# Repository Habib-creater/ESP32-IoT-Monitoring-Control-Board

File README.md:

# 4-Layer ESP32 IoT Monitoring and Control Board

<p align="center">
  <strong>ESP32-WROOM-32D • Si7021 • Relay • USB • Qwiic • 4-Layer PCB</strong>
</p>

<p align="center">
  A custom 4-layer ESP32-based hardware platform integrating environmental
  sensing, wired connectivity, relay control, USB programming, and
  expansion interfaces.
</p>

<p align="center">
  <a href="docs/IOT_Schematic.pdf">Schematic</a> •
  <a href="bom/IOT_BOM.csv">BOM</a> •
  <a href="manufacturing/gerbers/">Gerbers</a> •
  <a href="hardware/kicad/">KiCad Files</a>
</p>

---

## Overview

The **4-Layer ESP32 IoT Monitoring and Control Board** is a custom
embedded hardware platform built around the **ESP32-WROOM-32D** module.

The board combines environmental sensing through the **Si7021-A20**,
serial and wired interfaces, relay control, USB connectivity, Qwiic
expansion, and general-purpose GPIO in a compact 4-layer PCB design.

The complete hardware package is included in this repository, covering
the native **KiCad project**, electrical schematic, PCB layout, BOM,
Gerber and drill manufacturing files, pick-and-place data, and PCB
documentation.

> **Status:** Design files and manufacturing outputs included.

---

## Quick Access

| Resource | Description |
|---|---|
|  [Schematic PDF](docs/IOT_Schematic.pdf) | Complete electrical schematic |
|  [Bill of Materials](bom/IOT_BOM.csv) | Component BOM |
|  [Gerber & Drill Files](manufacturing/gerbers/) | PCB manufacturing outputs |
|  [KiCad Project](hardware/kicad/) | Native KiCad design files |
|  [PCB Images](docs/images/) | 3D renders and layer views |
|  [Pick-and-Place Data](manufacturing/pick-and-place/) | Component placement data |
|  [ERC / DRC Reports](docs/images/) | Design verification screenshots |

---

## Key Features

| Feature | Details |
|---|---|
| **Main Controller** | ESP32-WROOM-32D |
| **Environmental Sensor** | Si7021-A20 |
| **Sensor Interface** | I²C |
| **Serial / Expansion** | UART / GPIO |
| **Relay Control** | RT314A05 relay |
| **USB** | USB 2.0 Type-C interface |
| **Expansion** | Qwiic connector |
| **PCB** | 4-layer PCB |
| **EDA Software** | KiCad |
| **Manufacturing Data** | Gerber + PTH/NPTH drill files |
| **Assembly Data** | Top and bottom pick-and-place files |

---

## PCB Preview

### 3D Board Render

### Alternative 3D View

### Bottom 3D View

---

## PCB Layer Views

### Front Copper / Layout

### Inner Layer 1

### Inner Layer 2

### Bottom Layer

---

## Hardware Architecture

The design brings together several functional blocks around the ESP32
controller.

### ESP32-WROOM-32D

The **ESP32-WROOM-32D** provides the primary processing and wireless
connectivity platform for the board.

### Environmental Sensing

The **Si7021-A20** provides digital environmental sensing through an
I²C interface.

### Relay Control

A **RT314A05 relay** provides a dedicated switched-output function with
associated transistor drive circuitry.

### USB and Programming

The board includes a **USB Type-C USB 2.0 interface** and associated
USB interface circuitry.

### Qwiic Expansion

A **Qwiic connector** provides an additional I²C expansion interface.

---

## PCB Design

The board is implemented as a **4-layer PCB** using **KiCad**.

### PCB Characteristics

- 4-layer PCB architecture
- ESP32-WROOM-32D module
- Environmental sensor interface
- Relay control circuitry
- USB Type-C interface
- Qwiic expansion
- Dedicated internal copper layers
- Compact component placement
- Through-hole and surface-mount components
- PTH and NPTH manufacturing data

---

## Design Files

The native KiCad project is located in:

[**hardware/kicad/**](hardware/kicad/)

### Main Files

| File | Description |
|---|---|
| `IOT.kicad_pro` | KiCad project |
| `IOT.kicad_sch` | Schematic source |
| `IOT.kicad_pcb` | PCB layout |

---

## Schematic

The exported electrical schematic is available as:

###  [View IOT Schematic PDF](docs/IOT_Schematic.pdf)

The schematic documents the ESP32 controller, environmental sensor,
USB interface, relay control, Qwiic interface,
power circuitry, and associated support components.

---

## Bill of Materials

The current component BOM is available here:

###  [View / Download IOT BOM](bom/IOT_BOM.csv)

The BOM contains the component references, quantities, values,
footprints, and associated component information from the design.

---

## Manufacturing Outputs

The generated manufacturing package is available under:

###  [Gerber & Drill Files](manufacturing/gerbers/)

The package contains:

- Front copper
- Back copper
- Inner copper layer 1
- Inner copper layer 2
- Front solder mask
- Back solder mask
- Front silkscreen
- Back silkscreen
- Front solder paste
- Back solder paste
- Board outline
- PTH drill data
- NPTH drill data
- Gerber job file

---

## Pick-and-Place Data

Assembly placement data is available in:

[**manufacturing/pick-and-place/**](manufacturing/pick-and-place/)

The repository contains separate top-side and bottom-side component
placement files.

---

## Design Verification

Design verification artifacts included with the project:

### ERC

### DRC

---

## Project Status

| Item | Status |
|---|---|
| Schematic | ✅ Completed |
| PCB Layout | ✅ Completed |
| PCB Layer Count | ✅ 4-layer |
| KiCad Project | ✅ Included |
| BOM | ✅ Included |
| Gerber Files | ✅ Generated |
| Drill Files | ✅ Generated |
| Pick-and-Place Data | ✅ Included |
| ERC Documentation | ✅ Included |
| DRC Documentation | ✅ Included |
| PCB Documentation | ✅ Included |

---

## Repository Structure

```text
.
├── hardware/
│   └── kicad/
│       ├── IOT.kicad_pro
│       ├── IOT.kicad_sch
│       └── IOT.kicad_pcb
│
├── manufacturing/
│   ├── gerbers/
│   │   ├── IOT-F_Cu.gbr
│   │   ├── IOT-In1_Cu.gbr
│   │   ├── IOT-In2_Cu.gbr
│   │   ├── IOT-B_Cu.gbr
│   │   ├── IOT-F_Mask.gbr
│   │   ├── IOT-B_Mask.gbr
│   │   ├── IOT-F_Silkscreen.gbr
│   │   ├── IOT-B_Silkscreen.gbr
│   │   ├── IOT-F_Paste.gbr
│   │   ├── IOT-B_Paste.gbr
│   │   ├── IOT-Edge_Cuts.gbr
│   │   ├── IOT-PTH.drl
│   │   ├── IOT-NPTH.drl
│   │   └── IOT-job.gbrjob
│   │
│   └── pick-and-place/
│       ├── IOT-top.pos
│       └── IOT-bottom.pos
│
├── bom/
│   └── IOT_BOM.csv
│
├── docs/
│   ├── images/
│   │   ├── 3D_front_1.png
│   │   ├── 3D_front_2.png
│   │   ├── 3D_BACK.png
│   │   ├── Layout_front_layer.png
│   │   ├── Layout_inner_layer_1.png
│   │   ├── Layout_inner_layer_2.png
│   │   ├── Layout_Bottom_layer.png
│   │   ├── ERC.png
│   │   └── DRC.png
│   │
│   └── IOT_Schematic.pdf
│
├── .gitignore
├── CONTRIBUTING.md
├── LICENSE
└── README.md
```

---

## Acknowledgements

This repository contains the hardware design package for the
4-Layer ESP32 IoT Monitoring and Control Board.

The repository includes the native KiCad source files together with
the associated schematic, PCB documentation, BOM, manufacturing
outputs, and assembly data.

---

## Contributing

Contributions, design reviews, and hardware improvements are welcome.

For proposed revisions, keep the native KiCad design files and
associated documentation aligned with the corresponding hardware
revision.

---

## License

The hardware design files in this repository are licensed under the
**CERN Open Hardware Licence Version 2 - Strongly Reciprocal
(CERN-OHL-S-2.0)**.

The CERN-OHL-S-2.0 licence is a hardware-specific open-source licence
for sharing, modifying, and distributing covered hardware designs.

**Copyright © 2026 Habib Ur Rehman**

See [`LICENSE`](LICENSE) for the licence information associated with
this repository.

---

## Author

### Habib Ur Rehman

**Electronics Engineering**

Embedded systems, PCB design, microcontrollers, electronics hardware,
and hardware development.

### Connect

- **GitHub:** [Habib-creater](https://github.com/Habib-creater)
- **LinkedIn:** [Habib Ur Rehman](https://www.linkedin.com/in/habib-ur-rehman-8321182b4/)

---

<p align="center">
  <strong>4-Layer ESP32 IoT Monitoring and Control Board</strong><br>
  Custom ESP32 Embedded Hardware Platform
</p>

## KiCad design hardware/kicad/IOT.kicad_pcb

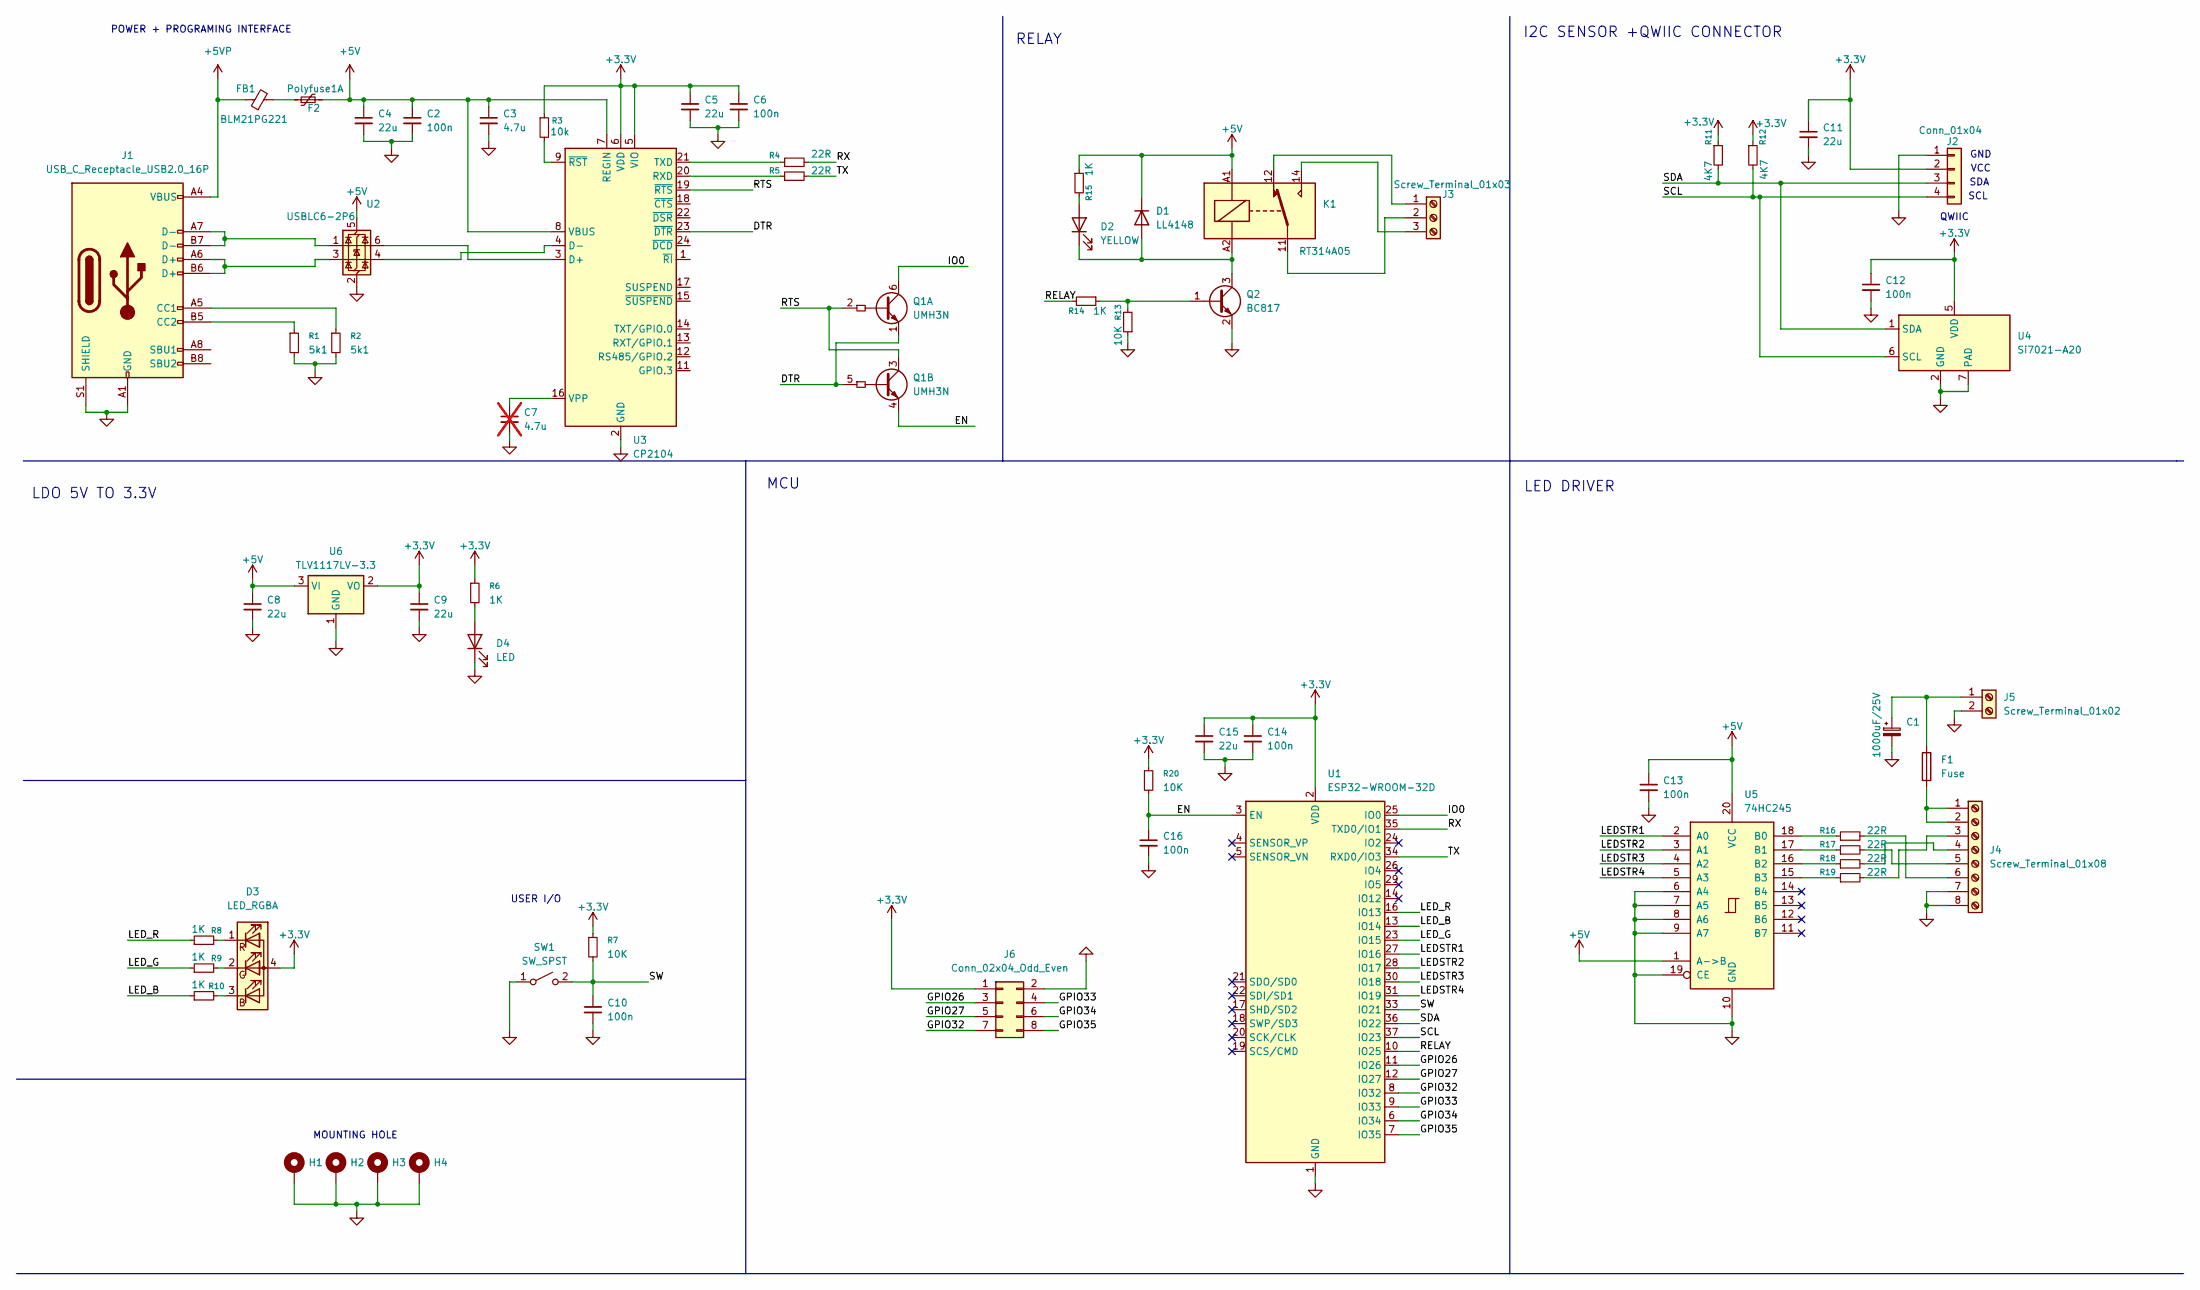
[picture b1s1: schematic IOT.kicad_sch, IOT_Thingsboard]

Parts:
C1: 1000uF/25V; CP_Radial_D10.0mm_P5.00mm
C2, C6, C10, C12, C13, C14, C16: 100n; C_0402_1005Metric_Pad0.74x0.62mm_HandSolder
C3: 4.7u; C_0805_2012Metric_Pad1.18x1.45mm_HandSolder
C4, C5, C8, C9, C11, C15: 22u; C_0805_2012Metric_Pad1.18x1.45mm_HandSolder
C7: 4.7u; C_0805_2012Metric_Pad1.18x1.45mm_HandSolder; not fitted
D1: LL4148; D_MiniMELF
D2: YELLOW; LED_0603_1608Metric_Pad1.05x0.95mm_HandSolder
D3: LED_RGBA; LED_RGB_Wuerth-PLCC4_3.2x2.8mm_150141M173100
D4: LED; LED_0603_1608Metric_Pad1.05x0.95mm_HandSolder
F1: Fuse; 696105003002
F2: Polyfuse1A; Fuse_1206_3216Metric_Pad1.42x1.75mm_HandSolder
FB1: BLM21PG221; L_0805_2012Metric
H1, H2, H3, H4: MountingHole_Pad; MountingHole_3.2mm_M3_Pad_Via
J1: USB_C_Receptacle_USB2.0_16P; USB_C_Receptacle_HRO_TYPE-C-31-M-12
J2: Conn_01x04; SPARKFUN_PRT-14417
J3: Screw_Terminal_01x03; TerminalBlock_Phoenix_MKDS-3-3-5.08_1x03_P5.08mm_Horizontal
J4: Screw_Terminal_01x08; TerminalBlock_Phoenix_MKDS-1,5-8_1x08_P5.00mm_Horizontal
J5: Screw_Terminal_01x02; TerminalBlock_Phoenix_MKDS-1,5-2_1x02_P5.00mm_Horizontal
J6: Conn_02x04_Odd_Even; PinHeader_2x04_P2.54mm_Vertical
K1: RT314A05; Relay_SPDT_Schrack-RT1-16A-FormC_RM5mm
Q1: UMH3N; SOT-363_SC-70-6
Q2: BC817; SOT-23
R1, R2: 5k1; R_0402_1005Metric_Pad0.72x0.64mm_HandSolder
R3: 10k; R_0402_1005Metric_Pad0.72x0.64mm_HandSolder
R4, R5, R16, R17, R18, R19: 22R; R_0402_1005Metric_Pad0.72x0.64mm_HandSolder
R6, R8, R9, R10, R14, R15: 1K; R_0402_1005Metric_Pad0.72x0.64mm_HandSolder
R7, R13, R20: 10K; R_0402_1005Metric_Pad0.72x0.64mm_HandSolder
R11, R12: 4K7; R_0402_1005Metric_Pad0.72x0.64mm_HandSolder
SW1: SW_SPST; SW_Push_1P1T_NO_CK_KMR2
U1: ESP32-WROOM-32D
U2: USBLC6-2P6; SOT-666
U3: CP2104; QFN-24-1EP_4x4mm_P0.5mm_EP2.6x2.6mm
U4: Si7021-A20; DFN-6-1EP_3x3mm_P1mm_EP1.5x2.4mm
U5: 74HC245; DIP-20_W7.62mm
U6: TLV1117LV-3.3; SOT-223-3_TabPin2

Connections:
+3.3V: C5.1, C6.1, C9.1, C11.1, C12.1, C14.1, C15.1, D3.4 (A), J2.2, J6.1, R3.1, R6.1, R7.1, R11.1, R12.1, R20.1, U1.2 (VDD), U3.5 (VIO), U3.6 (VDD), U4.5 (VDD), U6.2 (VO); also elsewhere on the board
+5V: C2.1, C3.1, C4.1, C8.1, C13.1, D1.1 (K), F2.2, K1.A1, R15.1, U2.5 (VBUS), U3.7 (REGIN), U3.8 (VBUS), U5.1 (A->B), U5.20 (VCC), U6.3 (VI)
+5VP: FB1.1, J1.A4 (VBUS), J1.A9 (VBUS), J1.B4 (VBUS), J1.B9 (VBUS)
/DTR: Q1.1 (E1), Q1.5 (B2), U3.23 (~DTR)
/EN: C16.1, Q1.4 (E2), R20.2, U1.3 (EN)
/GPIO26: J6.3, U1.11 (IO26); also elsewhere on the board
/GPIO27: J6.5, U1.12 (IO27); also elsewhere on the board
/GPIO32: J6.7, U1.8 (IO32); also elsewhere on the board
/GPIO33: J6.4, U1.9 (IO33); also elsewhere on the board
/GPIO34: J6.6, U1.6 (IO34); also elsewhere on the board
/GPIO35: J6.8, U1.7 (IO35); also elsewhere on the board
/IO0: Q1.6 (C1), U1.25 (IO0)
/LEDSTR1: U1.27 (IO16), U5.2 (A0)
/LEDSTR2: U1.28 (IO17), U5.3 (A1)
/LEDSTR3: U1.30 (IO18), U5.4 (A2)
/LEDSTR4: U1.31 (IO19), U5.5 (A3)
/LED_B: R10.1, U1.13 (IO14)
/LED_G: R9.1, U1.23 (IO15)
/LED_R: R8.1, U1.16 (IO13)
/RELAY: R14.2, U1.10 (IO25)
/RTS: Q1.2 (B1), Q1.3 (C2), U3.19 (~RTS)
/RX: R4.2, U1.35 (TXD0/IO1)
/SCL: J2.4, R12.2, U1.37 (IO23), U4.6 (SCL)
/SDA: J2.3, R11.2, U1.36 (IO22), U4.1 (SDA)
/SW: C10.1, R7.2, SW1.2 (B), U1.33 (IO21)
/TX: R5.2, U1.34 (RXD0/IO3)
GND: C1.2, C2.2, C3.2, C4.2, C5.2, C6.2, C7.2, C8.2, C9.2, C10.2, C11.2, C12.2, C13.2, C14.2, C15.2, C16.2, D4.1 (K), H1.1, H2.1, H3.1, H4.1, J1.A1 (GND), J1.A12 (GND), J1.B1 (GND), J1.B12 (GND), J1.S1 (SHIELD), J2.1, J4.7, J4.8, J5.2, J6.2, Q2.2 (E), R1.2, R2.2, R13.1, SW1.1 (A), U1.1 (GND), U1.15 (GND), U1.38 (GND), U1.39 (GND), U2.2 (GND), U3.2 (GND), U3.25 (GND), U4.2 (GND), U4.7 (PAD), U5.6 (A4), U5.7 (A5), U5.8 (A6), U5.9 (A7), U5.10 (GND), U5.19 (CE), U6.1 (GND); also elsewhere on the board
unnamed: D1.2 (A), D2.1 (K), K1.A2, Q2.3 (C)
unnamed: D2.2 (A), R15.2
unnamed: D3.3 (BK), R10.2
unnamed: D3.2 (GK), R9.2
unnamed: D3.1 (RK), R8.2
unnamed: D4.2 (A), R6.2
unnamed: F2.1, FB1.2
unnamed: J1.A5 (CC1), R2.1
unnamed: J1.B5 (CC2), R1.1
unnamed: J1.A6 (D+), J1.B6 (D+), U2.3 (I/O2)
unnamed: J1.A7 (D-), J1.B7 (D-), U2.1 (I/O1)
unnamed: J3.1, K1.12
unnamed: J3.2, K1.11
unnamed: J3.3, K1.14
unnamed: F1.2, J4.1, J4.2
unnamed: J4.3, R19.2
unnamed: J4.4, R18.2
unnamed: J4.5, R17.2
unnamed: J4.6, R16.2
unnamed: C1.1, F1.1, J5.1
unnamed: Q2.1 (B), R13.2, R14.1
unnamed: U2.6 (I/O1), U3.3 (D+)
unnamed: U2.4 (I/O2), U3.4 (D-)
unnamed: R5.1, U3.20 (RXD)
unnamed: R4.1, U3.21 (TXD)
unnamed: C7.1, U3.16 (VPP)
unnamed: R3.2, U3.9 (~RST)
unnamed: R16.1, U5.18 (B0)
unnamed: R17.1, U5.17 (B1)
unnamed: R18.1, U5.16 (B2)
unnamed: R19.1, U5.15 (B3)

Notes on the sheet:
LDO 5V TO 3.3V
POWER + PROGRAMING INTERFACE
LED DRIVER
QWIIC
MOUNTING HOLE
MCU
RELAY
SCL
GND
VCC
SDA
USER I/O
I2C SENSOR +QWIIC CONNECTOR

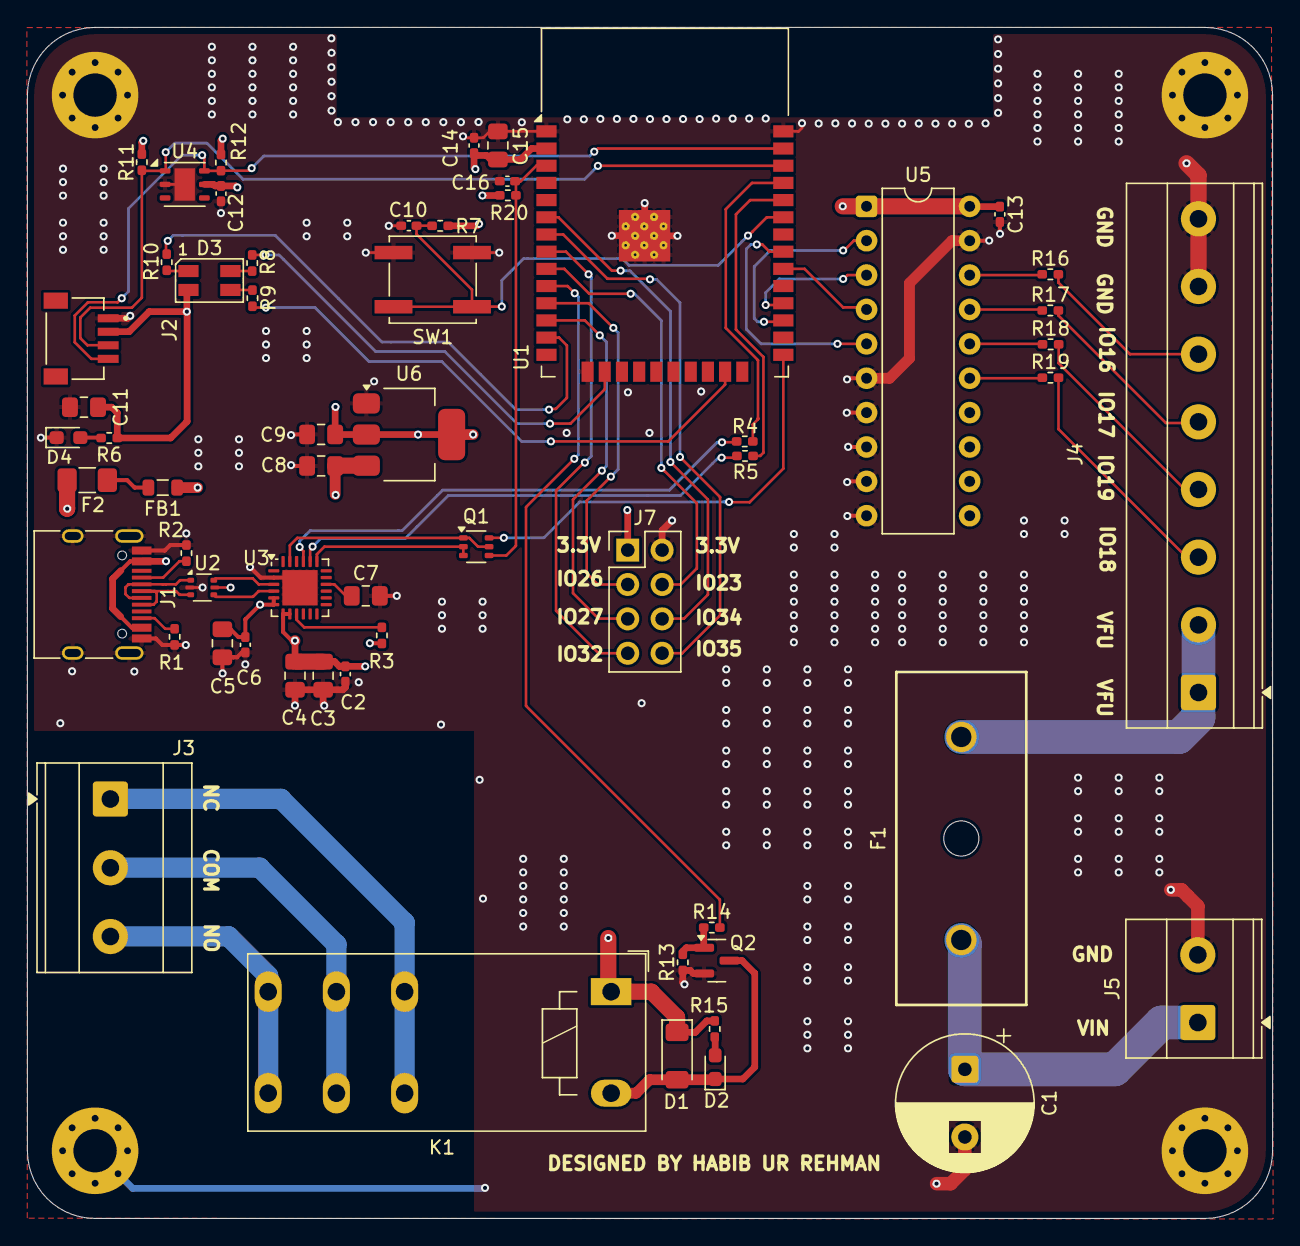
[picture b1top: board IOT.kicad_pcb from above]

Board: 4 copper layers, 92.0 x 88.0 mm, 63 parts (0 on the bottom side), 58 nets.

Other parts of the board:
J7: Conn_02x04_Odd_Even; PinHeader_2x04_P2.54mm_Vertical

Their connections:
+3.3V: J7.1; also elsewhere on the board
/GPIO26: J7.3; also elsewhere on the board
/GPIO27: J7.5; also elsewhere on the board
/GPIO32: J7.7; also elsewhere on the board
/GPIO33: J7.4; also elsewhere on the board
/GPIO34: J7.6; also elsewhere on the board
/GPIO35: J7.8; also elsewhere on the board
GND: J7.2; also elsewhere on the board

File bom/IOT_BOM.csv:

Reference,Qty,Value,DNP,Exclude from BOM,Exclude from Board,Footprint,Description,Manufacturer,Manufacturer Part No ,Supplier,Supplier Part No,Supplier Link,
C1,1,1000uF/25V,,,,Capacitor_THT:CP_Radial_D10.0mm_P5.00mm,CAP ALUM POLY 1000UF 20% 25V TH,KEMET,A750MV108M1EAAE014,DigiKey,399-A750MV108M1EAAE014-ND,https://www.digikey.com/en/products/detail/kemet/A750MV108M1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,
"C2,C6,C10,C12,C13,C14,C16",7,100n,,,,Capacitor_SMD:C_0402_1005Metric_Pad0.74x0.62mm_HandSolder,CAP CER 100NF 10V X7R 0402,Samsung Electro-Mechanics,CL05B104KP5VPNC,DigiKey,1276-CL05B104KP5VPNCCT-ND,https://www.digikey.com/en/products/detail/samsung-electro-m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,
C3,1,4.7u,,,,Capacitor_SMD:C_0805_2012Metric_Pad1.18x1.45mm_HandSolder,CAP CER 4.7UF 16V X5R 0805,Samsung Electro-Mechanics,CL21A475KOFNNNE,DigiKey,1276-1065-1-ND,https://www.digikey.com/en/products/detail/tdk/C1005X5R1A475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,https://www.digikey.com/en/products/detail/samsung-electro-m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
"C4,C5,C8,C9,C11,C15",6,22u,,,,Capacitor_SMD:C_0805_2012Metric_Pad1.18x1.45mm_HandSolder,CAP CER 22UF 16V X5R 0805,Samsung Electro-Mechanics,CL21A226KOQNNNE,DigiKey,1276-6526-1-ND,https://www.digikey.com/en/products/detail/samsung-electro-m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,
C7,1,4.7u,DNP,Excluded from BOM,,Capacitor_SMD:C_0805_2012Metric_Pad1.18x1.45mm_HandSolder,CAP CER 4.7UF 16V X5R 0805,Samsung Electro-Mechanics,CL21A475KOFNNNE,DigiKey,1276-1065-1-ND,https://www.digikey.com/en/products/detail/samsung-electro-m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,
D1,1,LL4148,,,,Diode_SMD:D_MiniMELF,SWITCHING DIODE 0.3A 100V SOD-80,Lumimax Optoelectronic Technology,LL4148,DigiKey,4491-LL4148TR-ND,https://www.digikey.com/en/products/detail/lumimax-optoelect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,
D2,1,YELLOW,,,,LED_SMD:LED_0603_1608Metric_Pad1.05x0.95mm_HandSolder,LED YELLOW 0603 SMD,Vishay Semiconductor Opto Division,TLMY1100-GS15,DigiKey,751-TLMY1100-GS15CT-ND,https://www.digikey.com/en/products/detail/vishay-semiconduc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,
D3,1,LED_RGBA,,,,LED_SMD:LED_RGB_Wuerth-PLCC4_3.2x2.8mm_150141M173100,LED RGB CLEAR 3528 SMD,Würth Elektronik,150141M173100,DigiKey,732-4998-1-ND,https://www.digikey.com/en/products/detail/w%C3%BCrth-elektr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,
D4,1,LED,,,,LED_SMD:LED_0603_1608Metric_Pad1.05x0.95mm_HandSolder,LED RED 0603 SMD,Vishay Semiconductor Opto Division,VLMS1300-GS08,DigiKey,VLMS1300-GS08CT-ND,https://www.digikey.com/en/products/detail/vishay-semiconduc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,
F1,1,Fuse,,,,Fuse_1:696105003002,FUSEHOLDER BLOCKS - PCB - CLIP C,Würth Elektronik,6.96E+11,DigiKey,732-11373-ND,https://www.digikey.com/en/products/detail/w%C3%BCrth-elektr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,
F2,1,Polyfuse1A,,,,Fuse:Fuse_1206_3216Metric_Pad1.42x1.75mm_HandSolder,"Polymeric PTC Resettable Fuse 8V 1.1 A Ih Surface Mount 1206 (3216 Metric), Concave",Littelfuse Inc.,1206L110THYR,DigiKey,F3371CT-ND,https://www.digikey.com/en/products/detail/littelfuse-inc/12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,
FB1,1,BLM21PG221,,,,Inductor_SMD:L_0805_2012Metric,FERRITE BEAD 220 OHM 0805 1LN,Murata Electronics,BLM21PG221SN1D,DigiKey,490-1054-1-ND,https://www.digikey.com/en/products/detail/murata-electronic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,
"H1,H2,H3,H4",4,MountingHole_Pad,,Excluded from BOM,,MountingHole:MountingHole_3.2mm_M3_Pad_Via,Mounting Hole with connection,,,,,,
J1,1,USB_C_Receptacle_USB2.0_16P,,,,Connector_USB:USB_C_Receptacle_HRO_TYPE-C-31-M-12,CONN RCPT Type-C 16POS SMD,Korean Hroparts Elec,TYPE-C-31-M-12,LCSC,C165948,https://www.lcsc.com/product-detail/USB-Type-C_Korean-Hropar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,
J2,1,Conn_01x04,,,,QWIIC CONNECTOR 4P:SPARKFUN_PRT-14417,QWIIC CONNECTOR SMD 4-PIN,SparkFun Electronics,14417,DigiKey,1568-14417-ND,https://www.digikey.com/en/products/detail/sparkfun-electron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,
J3,1,Screw_Terminal_01x03,,,,TerminalBlock_Phoenix:TerminalBlock_Phoenix_MKDS-3-3-5.08_1x03_P5.08mm_Horizontal,TERM BLK 3P SIDE ENT 5.08MM PCB,Phoenix Contact,1729131,DigiKey,277-1248-ND,https://www.digikey.com/en/products/detail/phoenix-contact/1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,
J4,1,Screw_Terminal_01x08,,,,"TerminalBlock_Phoenix:TerminalBlock_Phoenix_MKDS-1,5-8_1x08_P5.00mm_Horizontal",TERM BLK 8POS SIDE ENTRY 5MM PCB,Phoenix Contact,1711084,DigiKey,277-1025-ND,https://www.digikey.com/en/products/detail/phoenix-contact/1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,
J5,1,Screw_Terminal_01x02,,,,"TerminalBlock_Phoenix:TerminalBlock_Phoenix_MKDS-1,5-2_1x02_P5.00mm_Horizontal",TERM BLK 2POS SIDE ENTRY 5MM PCB,Phoenix Contact,1715022,DigiKey,277-1258-ND,https://www.digikey.com/en/products/detail/phoenix-contact/1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,
J6,1,Conn_02x04_Odd_Even,,,,Connector_PinHeader_2.54mm:PinHeader_2x04_P2.54mm_Vertical,CONN HEADER VERT 8POS 2.54MM,Samtec Inc.,TD-104-T-A,DigiKey,612-TD-104-T-A-ND,https://www.digikey.com/en/products/detail/samtec-inc/TD-104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,
K1,1,RT314A05,,,,Relay_THT:Relay_SPDT_Schrack-RT1-16A-FormC_RM5mm,"Schrack RT1 relay, bistable single pole dual throw, single DC coil, 5V",TE Connectivity Potter & Brumfield Relays,RT314A05,DigiKey,PB1695-ND,https://www.digikey.com/en/products/detail/te-connectivity-p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,
Q1,1,UMH3N,,,,Package_TO_SOT_SMD:SOT-363_SC-70-6,TRANS PREBIAS 2NPN 50V UMT6,Rohm Semiconductor,UMH3NFHATN,DigiKey,UMH3NFHATNCT-ND,https://www.digikey.com/en/products/detail/rohm-semiconducto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,
Q2,1,BC817,,,,Package_TO_SOT_SMD:SOT-23,Bipolar (BJT) Transistor NPN 45 V 800 mA 100MHz 310 mW Surface Mount SOT-23,MCC (Micro Commercial Components),BC817-40-TP,DigiKey,BC817-40-TPMSCT-ND,https://www.digikey.com/en/products/detail/mcc-micro-commerc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,
"R1,R2",2,5k1,,,,Resistor_SMD:R_0402_1005Metric_Pad0.72x0.64mm_HandSolder,RES 5.1K OHM 1% 1/16W 0402,YAGEO,RC0402FR-075K1L,DigiKey,311-5.10KLRCT-ND,https://www.digikey.com/en/products/detail/yageo/RC0402FR-07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,
R3,1,10k,,,,Resistor_SMD:R_0402_1005Metric_Pad0.72x0.64mm_HandSolder,RES 10K OHM 1% 1/16W 0402,YAGEO,RC0402FR-0710KL,DigiKey,311-10.0KLRCT-ND,https://www.digikey.com/en/products/detail/yageo/RC0402FR-07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,
"R4,R5,R16,R17,R18,R19",6,22R,,,,Resistor_SMD:R_0402_1005Metric_Pad0.72x0.64mm_HandSolder,RES 22 OHM 1% 1/16W 0402,YAGEO,RC0402FR-0722RL,DigiKey,311-22.0LRCT-ND,https://www.digikey.com/en/products/detail/yageo/RC0402FR-07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,
"R6,R8,R9,R10,R14,R15",6,1K,,,,Resistor_SMD:R_0402_1005Metric_Pad0.72x0.64mm_HandSolder,RES 1K OHM 1% 1/16W 0402,YAGEO,RC0402FR-071KL,DigiKey,311-1.00KLRCT-ND,https://www.digikey.com/en/products/detail/yageo/RC0402FR-07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,
"R7,R13,R20",3,10K,,,,Resistor_SMD:R_0402_1005Metric_Pad0.72x0.64mm_HandSolder,RES 10K OHM 1% 1/16W 0402,YAGEO,RC0402FR-0710KL,DigiKey,311-10.0KLRCT-ND,https://www.digikey.com/en/products/detail/yageo/RC0402FR-07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,
"R11,R12",2,4K7,,,,Resistor_SMD:R_0402_1005Metric_Pad0.72x0.64mm_HandSolder,RES 4.7K OHM 1% 1/16W 0402,YAGEO,RC0402FR-074K7L,DigiKey,311-4.7KLRCT-ND,https://www.digikey.com/en/products/detail/yageo/RC0402FR-07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,
SW1,1,SW_SPST,,,,Button_Switch_SMD:SW_Push_1P1T_NO_CK_KMR2,SWITCH TACTILE SPST-NO 0.05A 32V,C&K,KMR211G LFS,DigiKey,108-KMR211GLFSCT-ND,https://www.digikey.com/en/products/detail/c-k/KMR211G-LFS/550475,
U1,1,ESP32-WROOM-32D,,,,RF_Module:ESP32-WROOM-32D,"RF Module, ESP32-D0WD SoC, Wi-Fi 802.11b/g/n, Bluetooth, BLE, 32-bit, 2.7-3.6V, onboard antenna, SMD",ESPRESSIF,ESP32-WROOM-32D-N4,LCSC,C473012,https://www.lcsc.com/product-detail/C473012.html?s_z=n_q_ESP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,
U2,1,USBLC6-2P6,,,,Package_TO_SOT_SMD:SOT-666,TVS DIODE 5.25VWM 17VC SOT666,STMicroelectronics,USBLC6-2P6,DigiKey,497-5026-1-ND,https://www.digikey.com/en/products/detail/stmicroelectronic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,
U3,1,CP2104,,,,Package_DFN_QFN:QFN-24-1EP_4x4mm_P0.5mm_EP2.6x2.6mm,IC SGL USB-TO-UART BRIDGE 24QFN,Silicon Labs,CP2104-F03-GMR,DigiKey,336-4146-1-ND,https://www.digikey.com/en/products/detail/silicon-labs/CP21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,
U4,1,Si7021-A20,,,,Package_DFN_QFN:DFN-6-1EP_3x3mm_P1mm_EP1.5x2.4mm,SENS HUMID/TEMP 3.6V I2C 3% 6DFN,Silicon Labs,SI7021-A20-IMR,DigiKey,336-5200-1-ND,https://www.digikey.com/en/products/detail/silicon-labs/SI70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,
U5,1,74HC245,,,,Package_DIP:DIP-20_W7.62mm,IC TXRX 2V/6V 20-PDIP,Texas Instruments,CD74HC245E,DigiKey,296-12800-5-ND,https://www.digikey.com/en/products/detail/texas-instruments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,
U6,1,TLV1117LV-3.3,,,,Package_TO_SOT_SMD:SOT-223-3_TabPin2,"3.3V Positive Fixed SOT-223-3 Voltage Regulators - Linear, Low Drop Out (LDO) Regulators ",TECH PUBLIC,TPTLV1117LV33DCYR,LCSC,C52146079,https://www.lcsc.com/product-detail/C52146079.html?s_z=n_q_l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,
